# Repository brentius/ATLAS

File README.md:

# ATLAS
*Written in the prophetic perfect tense to give myself some motivation*

ATLAS (Atomic-scale Tunneling and Local Analysis Syste*) is a low-cost scanning tunneling microscope (STM) build inspired by Dimsmary's OpenSTM project (https://github.com/Dimsmary/OpenSTM), with the end goal to accurately image carbon atoms on the lattice of a sample of HOPG.

## File Structure

```
pcb/
code/
cad/
sim/
README.md
LICENSE-HARDWARE
LICENSE-SOFTWARE
.gitignore
```
## Licenses

Hardware design files in `pcb/` and `cad/`, including schematics, PCB layouts,
footprints, and mechanical designs, are licensed under the
[CERN Open Hardware Licence Version 2 – Strongly Reciprocal](LICENSE-HARDWARE)
(`CERN-OHL-S-2.0`). Hardware circuit netlists in `sim/` are covered by the same
license.

Software in `code/` and simulation scripts in `sim/` are licensed under the
[GNU General Public License Version 3](LICENSE-SOFTWARE) (`GPL-3.0-only`).

## How does ATLAS work?
ATLAS is a **scanning tunneling microscope** (STM). Essentially, you have a tip of some hard conductive material (Pt-Ir in this case) that is brought within nanometers of a sample, and very slowly moved along it. As the tip moves along the sample, electrons can tunnel from the atoms in the sample to the tip, which creates a miniscule current. What an STM does is take that current and through PCB wizardry amplify it into something readable, and from that construct a 3D image of the sample at the atomic scale.
# The project itself...
## A bit about this project
*For a more detailed log, refer to my blog at brentius.github.io/blog.*

I first started thinking of this project after my GCSEs in late June 2026, but I really didn't start work until September/October of that year. I'd been (very slowly) working my way through Griffths's *Introduction to Quantum Mechanics* the year before, and I thought it'd be a great idea to simply have fun and play around with quantum tunneling for a bit. I also wanted to do an actual *practical* project, because I absolutely adore PCB design - it's almost theraputic (triggers the same bits of my brain as those iPad games where you need to connect the dots without the lines crossing each other). But before I started any work, the project had to satisfy a few criteria:

1. Is it cool or not? Self explanatory, and I think I made the right choice.
2. Will it kill me? No matter how cool a project, there's not much use in doing it if I die in the process; I'd quite like to stay alive, thank you very much.
3. What can I learn from it? I've always been itching to try my hand at FPGAs, and this project was the perfect opportunity to do so.
4. How expensive will it be? At the end of the day, I don't have infinite funding; if I fry a PCB, or I break a Pt-Ir tip, it's coming out of my own pocket. Not ideal.

The only project that really satisfied all 4 criteria was building an STM, so I got to work on it. I was on vacation in Spain and Sweden during July, so there really wasn't much I could do except for starting to work on the PCBs. And my god, were these a pain.

ATLAS consists of 3 PCBs:
1. **TIA/preamp**. This uses an OPA828 DAC, along with a 100M resistor, to take in the *absolutely miniscule* current from electrons tunneling from the sample to the tip and amplify it by ~10e8 V/A, to get 15 volts running out of the back. This was actually one of the easier PCBs to design, mostly because of how few components there were. The main difficulty in designing the TIA board was physical routing - the current input trace had to be as short as possible and use as little copper as possible, and it also needed to be fenced off with the Great Wall of Vias (there's probably a Latin joke to be made in there but frankly I'm too dumb to make it) to protect it from interference from other traces. This meant that the shape of the board itself was hard to design, as the resistor meant that the board was quite large in both X and Y; considering this had to sit on the scanner block, it was not ideal.
2. **Converter/Pmod carrier**. This was about the point where I figured out I was probably extremely out of my depth. The Converter acts as a translator between the FPGA and the analog circuitry; onboard there's a SAR ADC, which takes the output from the TIA and digitises it for a PID loop. There are also two DAC8734s, that generate the X/Y/Z scan and feedback drive voltages (10 volts). Meanwhile, the AD7521 IC handles the DAC for the stick-slip sliding mechanism. Pmod headers carry SPI and control lines to and from the FPGA. As you can probably tell, this board was an absolute nightmare to design, and is the cause of many sleepless nights I will not get back.
3. **PSU**. All good things need power, and ATLAS is no exception. It runs on 15V - my original design called for a 45V rail to drive the tip movement for maximum range, but I decided against it for redundancy's sake - this project is already complicated enough without splitting 3 power rails (10, 15 and 45V).
### Damping
The PCBs were only one part of the challenge. A STM is an extremely sensitive instrument - after all, it's imaging individual atoms - even someone shouting next to it *will* throw the measurement off. To that end, ATLAS was built in one of the less used classrooms of Winchester College Mill, to keep foot traffic to a minimum; and a large sign was taped to the door telling people to keep their voices down. BUT THAT WASN'T ENOUGH! Any vibrations of the table would also throw the tip off by millimeters (matters a lot on the nanometer scale), so the whole system had to be on a damper.

The initial damper concept uses a frame, 8 springs and a 12lb slab of granite supporting the scanner assembly. The slab weight is adjustable rather than a fixed design requirement. No spring-rate or frequency measurement is recorded here, so the earlier 1Hz estimate is unverified. The [suspension calculation](sim/atlas_mechanics/SUSPENSION_BUDGET.md) and [comparison with other STM isolation designs](sim/atlas_mechanics/ISOLATION_OPTIONS.md) set out a modular trial of the spring stage, optional magnetic eddy-current damping and a short plate stack. Wind, sound and cable disturbances still need physical testing. I briefly considered building an enclosure with ANC, but I ultimately decided against it - the last thing I need is another signal processing challenge. It would be fun though...
## Assembly
*The instructions provided below are but a summary, and your version of ATLAS will probably not work if you just follow these. For a more detailed set of instructions, or if you'd like to see how I did it, please refer to brentius.github.io/blog.*

A full bill of materials can be found at ```BOM.md```.
### Part I. The Scanner Block
This is the scanner block - i.e. the block that actually does the scanning. One of the main insights I lifted from OpenSTM was to use a buzzer and a stick-slip mechanism to slowly increment the position of the tip, which franly I think was an insight of genius. Why a buzzer? While your typical linear actuators and belt drives work for 3D printing or CNC milling, an STM requires nanometer precision, which you physically can't achieve with a linear actuator. There's also the problem that linear actuators produce heat, which at nanometer scales, really throws the position off due to the joints expanding/contracting. We first quarter the 
#### Preparing the tip
Version 1 of ATLAS used a length of 80:20 Pt-Ir (platinum-iridium) wire that I simply cut at 45 degrees with a pair of sharp cutters. Boring, but it works.
# Meta Stuff
## Acknowledgements
# References

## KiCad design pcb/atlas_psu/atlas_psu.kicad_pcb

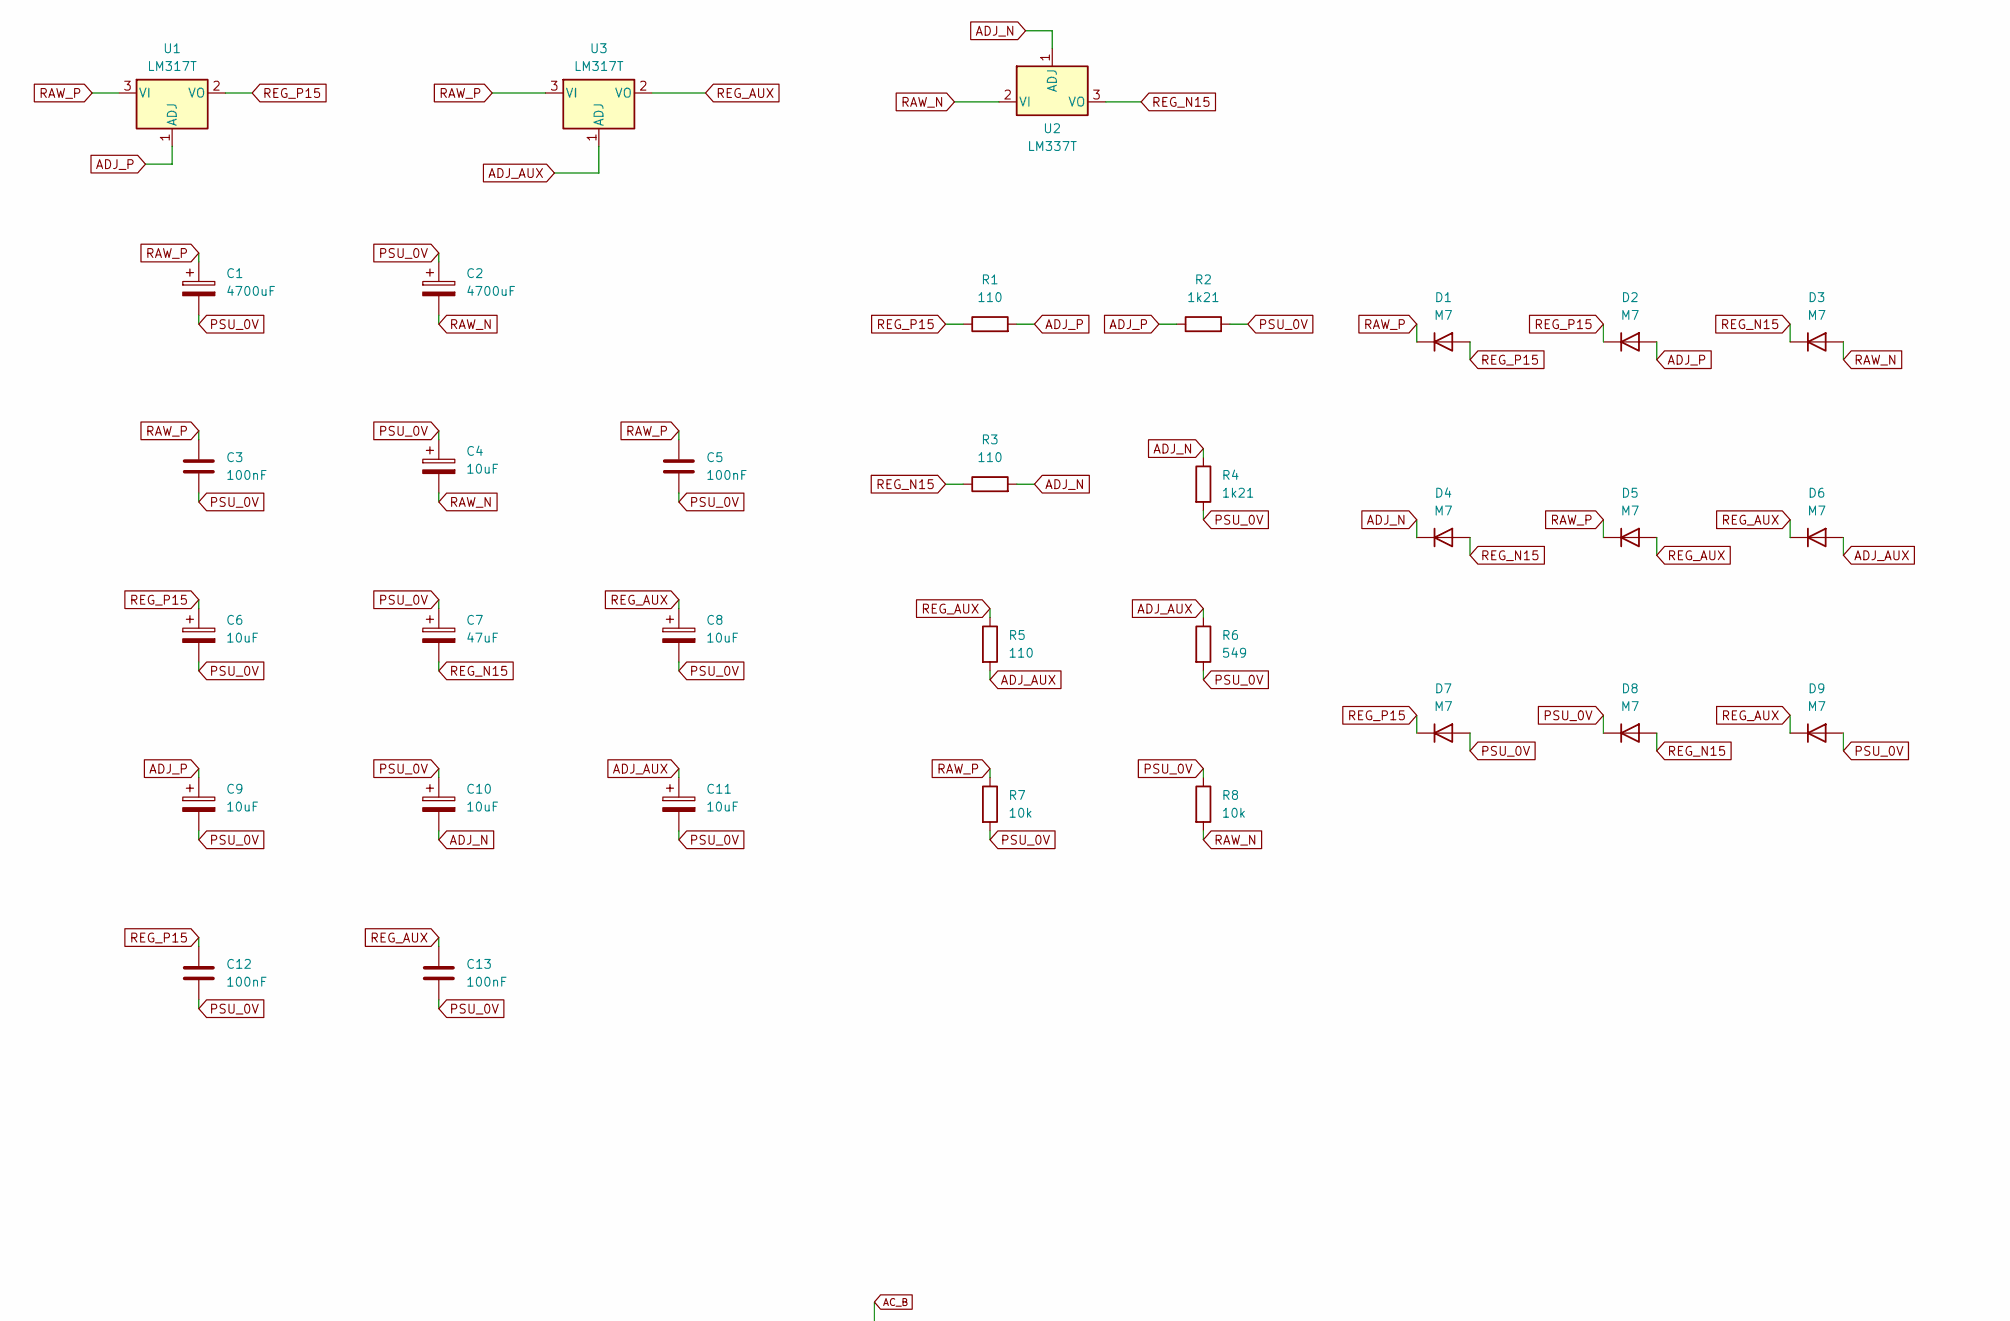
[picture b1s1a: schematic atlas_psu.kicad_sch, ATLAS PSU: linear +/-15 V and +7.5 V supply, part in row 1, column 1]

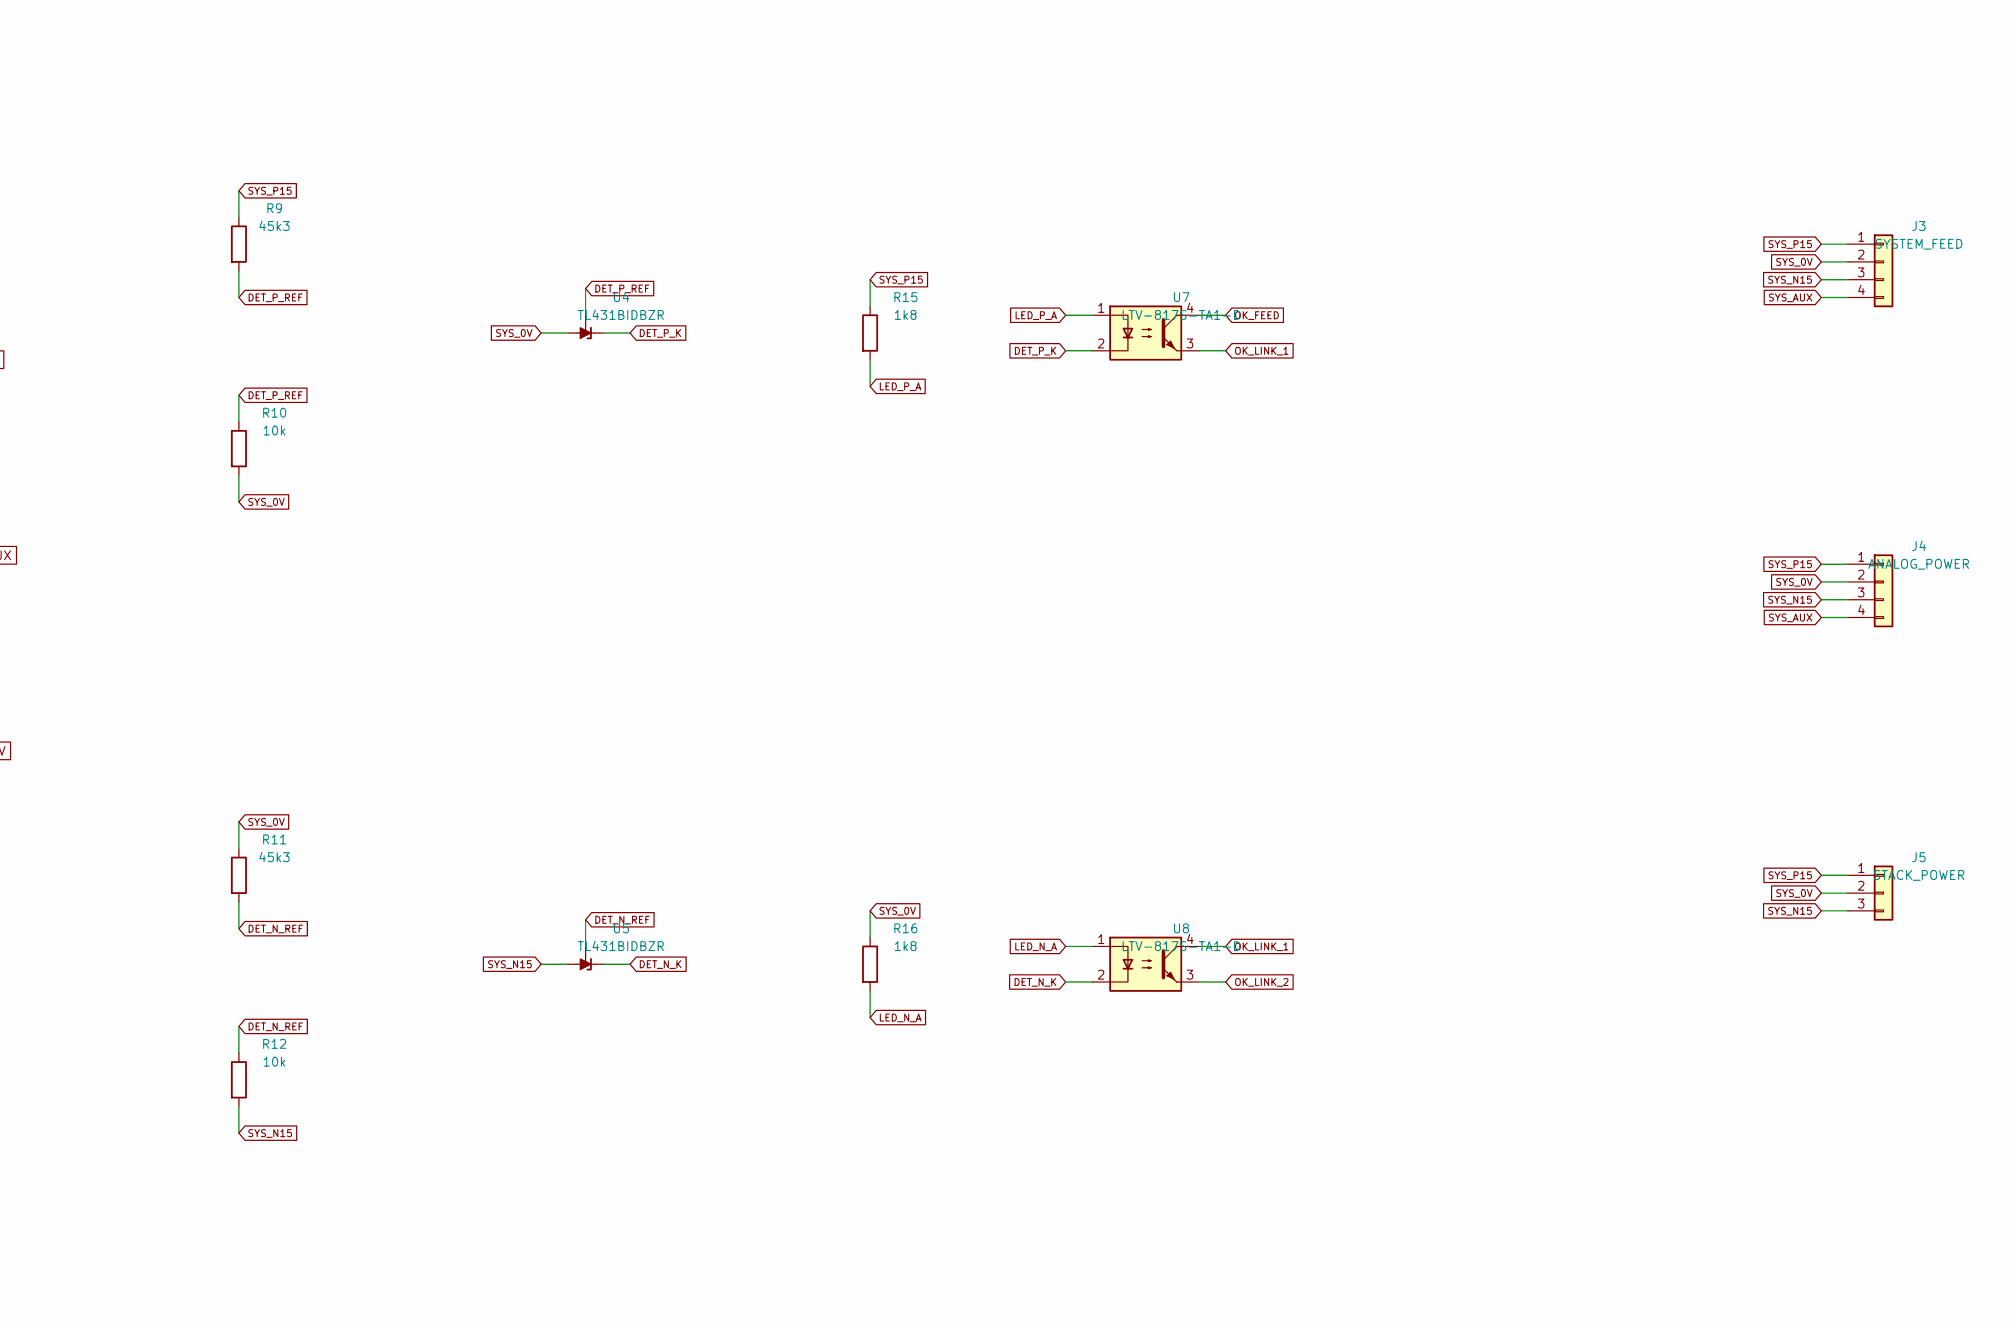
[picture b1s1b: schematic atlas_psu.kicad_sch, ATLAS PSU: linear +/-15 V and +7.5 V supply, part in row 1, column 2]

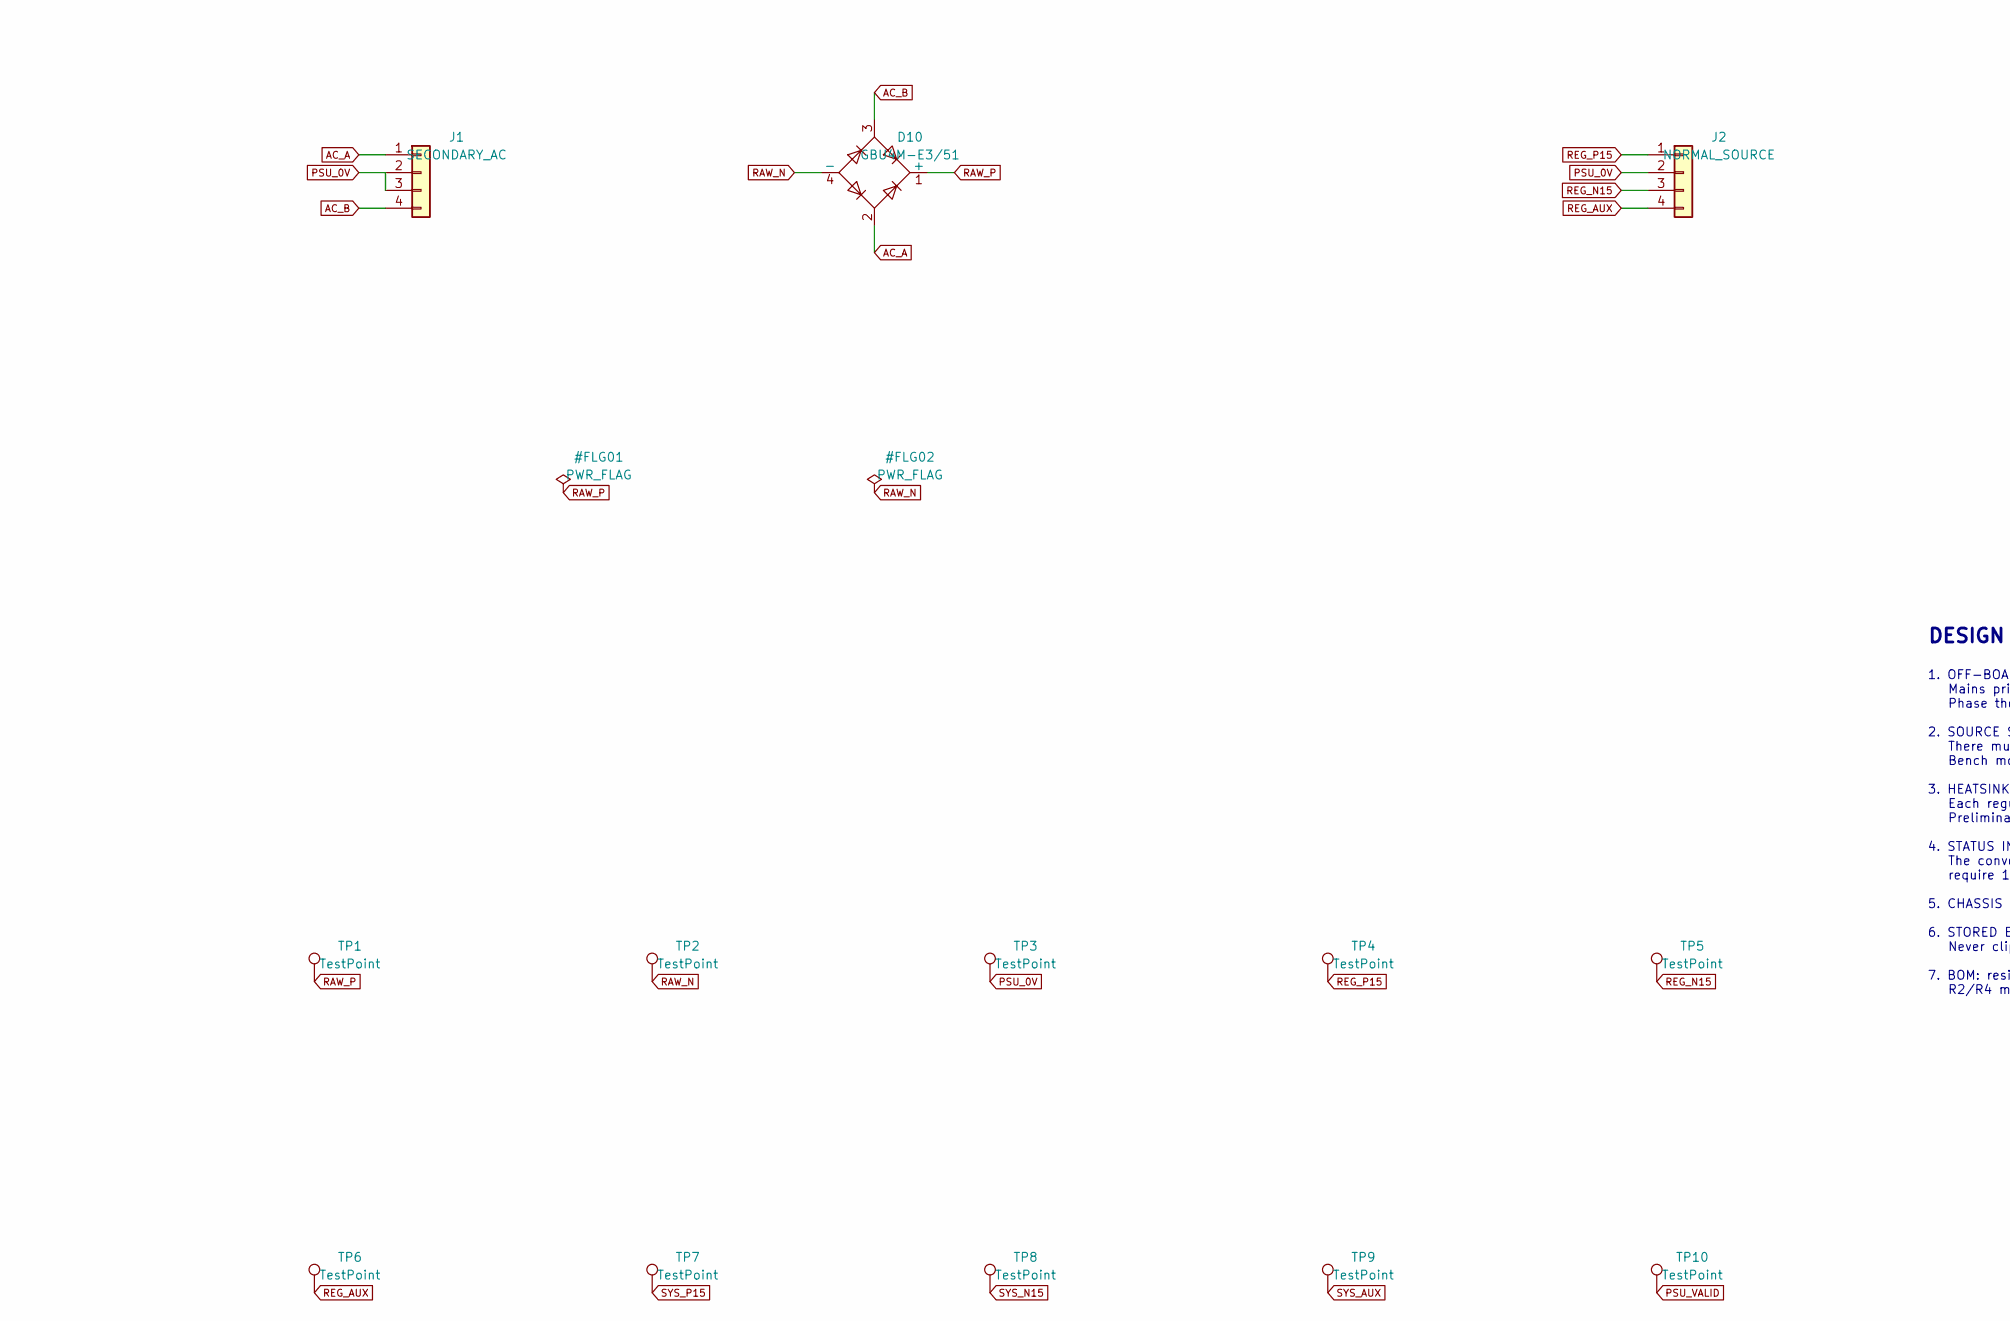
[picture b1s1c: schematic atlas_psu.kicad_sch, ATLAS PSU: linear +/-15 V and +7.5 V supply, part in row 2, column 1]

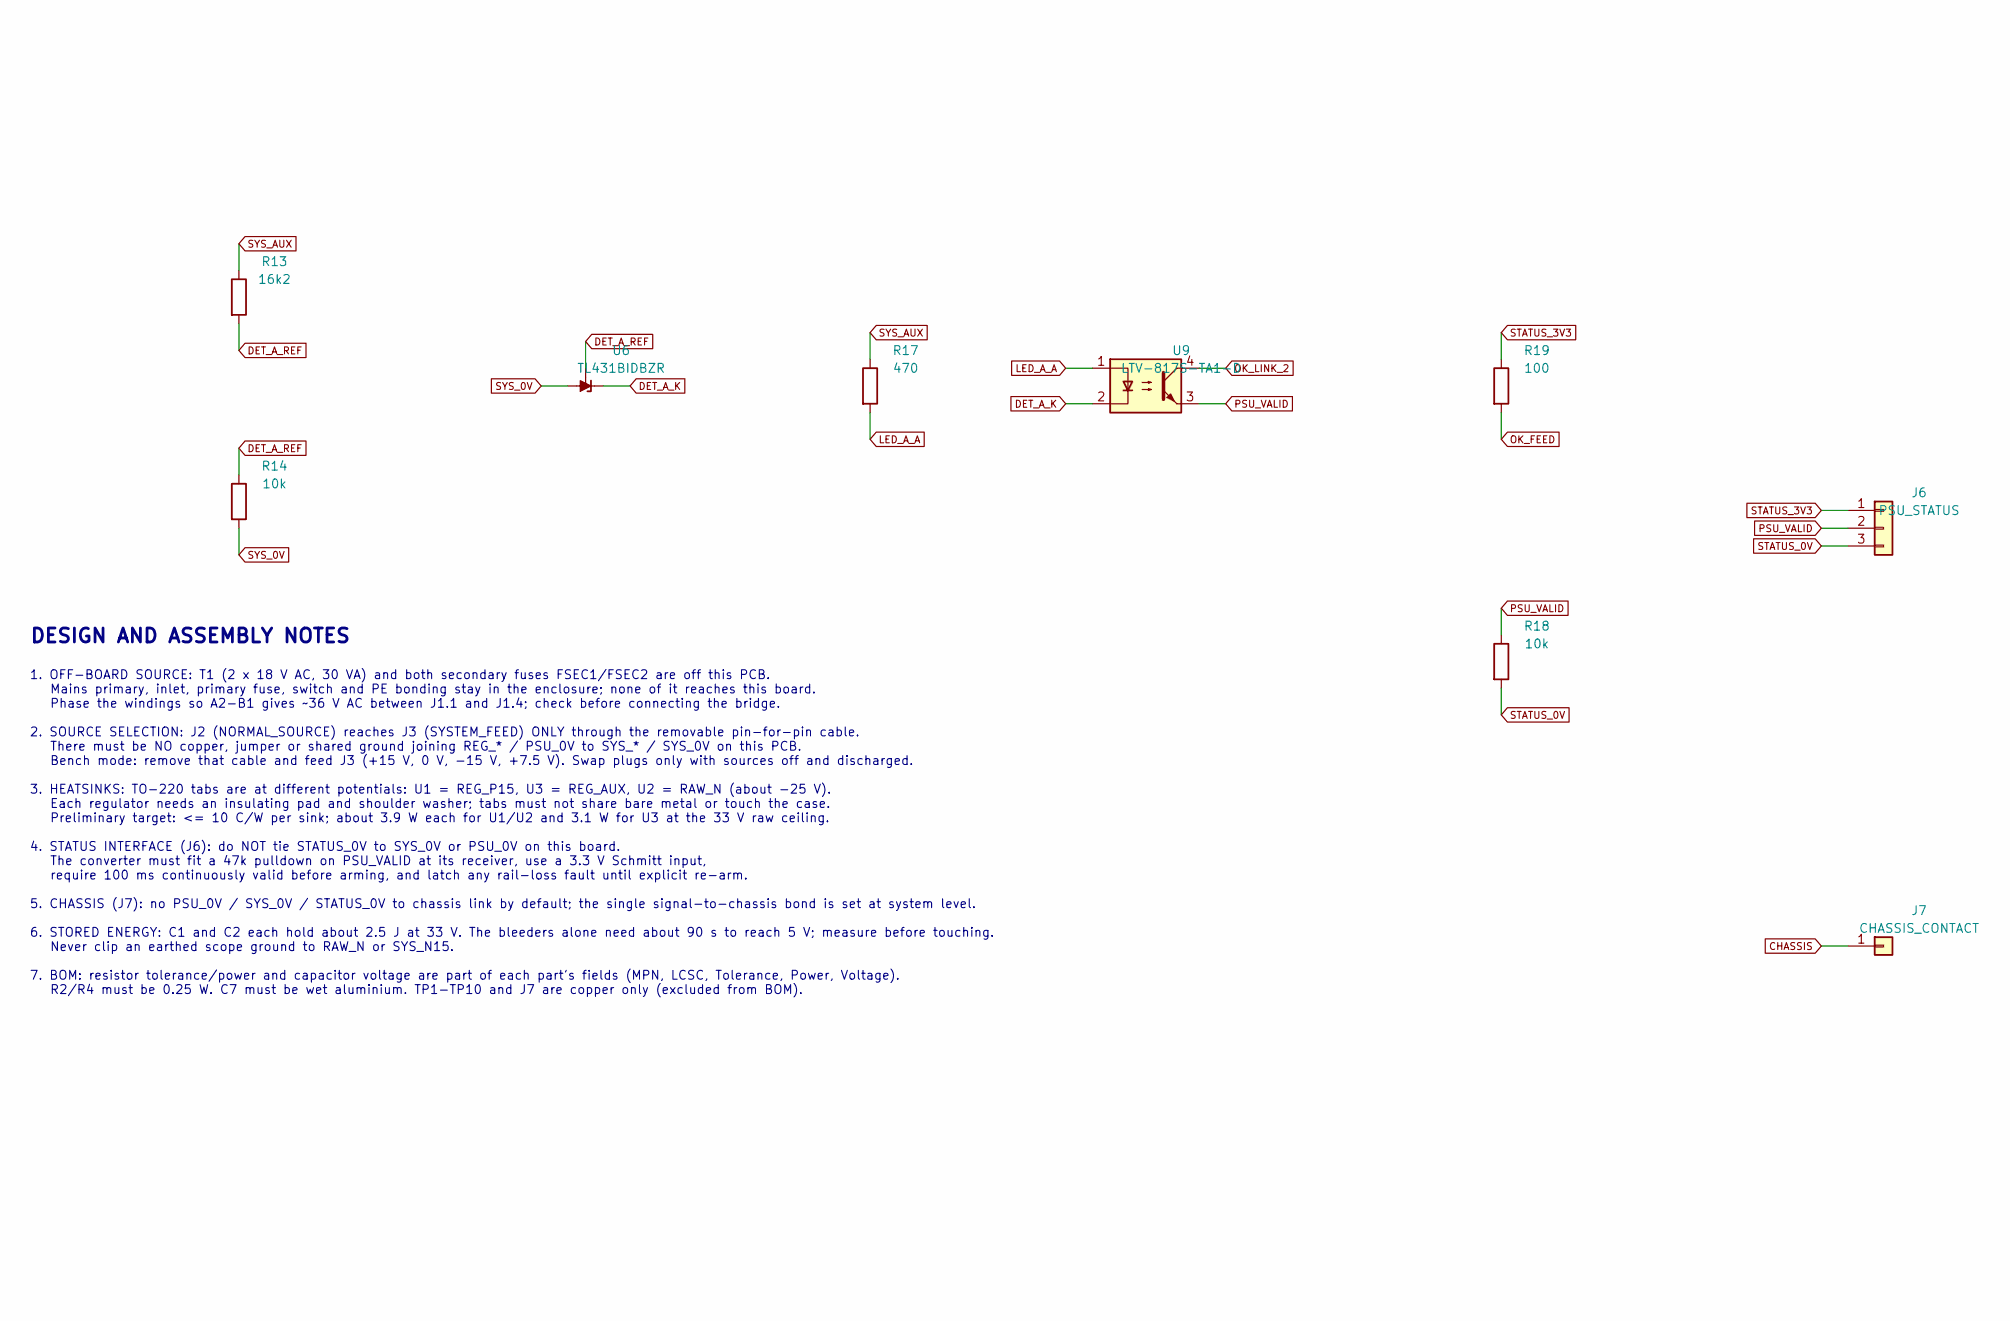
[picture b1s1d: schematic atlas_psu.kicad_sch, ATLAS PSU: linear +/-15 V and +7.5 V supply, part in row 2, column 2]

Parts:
C1, C2: 4700uF; CP_Radial_D30.0mm_P10.00mm_SnapIn; Tolerance 20%; Voltage 50V; MPN LGY1H472MELB30; LCSC C1582310
C3, C5, C12, C13: 100nF; C_0603_1608Metric; Tolerance 10%; Voltage 50V; MPN CL10B104KB8NNNC; LCSC C1591
C4, C6, C8, C9, C10, C11: 10uF; CP_Elec_6.3x5.4_Nichicon; Tolerance 20%; Voltage 50V; MPN UWT1H100MCL1GB; LCSC C445064
C7: 47uF; CP_Elec_6.3x7.7; Tolerance 20%; Voltage 50V; MPN UWT1H470MCL1GS; LCSC C445060
D1, D2, D3, D4, D5, D6, D7, D8, D9: M7; D_SMA; MPN M7; LCSC C95872
D10: GBU4M-E3/51; Diode_Bridge_Vishay_GBU; MPN GBU4M-E3/51; LCSC C3008977
J1: SECONDARY_AC; TerminalBlock_Phoenix_MKDS-1,5-4-5.08_1x04_P5.08mm_Horizont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; MPN MKDS 1,5/4-5,08
J2: NORMAL_SOURCE; JST_XH_B4B-XH-A_1x04_P2.50mm_Vertical; MPN B4B-XH-A; LCSC C41422491
J3: SYSTEM_FEED; JST_XH_B4B-XH-A_1x04_P2.50mm_Vertical; MPN B4B-XH-A; LCSC C41422491
J4: ANALOG_POWER; JST_XH_B4B-XH-A_1x04_P2.50mm_Vertical; MPN B4B-XH-A; LCSC C41422491
J5: STACK_POWER; JST_XH_B3B-XH-A_1x03_P2.50mm_Vertical; MPN B3B-XH-A(LF)(SN); LCSC C144394
J6: PSU_STATUS; JST_GH_SM03B-GHS-TB_1x03-1MP_P1.25mm_Horizontal; MPN SM03B-GHS-TB(LF)(SN); LCSC C514175
J7: CHASSIS_CONTACT; SolderWirePad_1x01_SMD_1.5x3mm
R1, R3, R5: 110; R_0603_1608Metric; Tolerance 0.1%; MPN RN73R1JTTD1100B25; LCSC C2508454
R2, R4: 1k21; R_0805_2012Metric; Tolerance 0.1%; MPN ERA-6VEB1211V; LCSC C3986344
R6: 549; R_0805_2012Metric; Tolerance 0.1%; MPN ERA-6AEB5490V; LCSC C2087831
R7, R8: 10k; R_2010_5025Metric; Tolerance 5%; MPN 2010W2J0103T4S; LCSC C20349
R9, R11: 45k3; R_0603_1608Metric; Tolerance 0.1%; MPN ERA-3AEB4532V; LCSC C3951453
R10, R12, R14, R18: 10k; R_0603_1608Metric; Tolerance 1%; MPN 0603WAF1002T5E; LCSC C25804
R13: 16k2; R_0603_1608Metric; Tolerance 1%; MPN RTT031622FTP; LCSC C103329
R15, R16: 1k8; R_1206_3216Metric; Tolerance 1%; MPN CRCW12061K80FKEBC; LCSC C4211031
R17: 470; R_1206_3216Metric; Tolerance 1%; MPN CR1206F44700G; LCSC C102199
R19: 100; R_0603_1608Metric; Tolerance 1%; MPN 0603WAF1000T5E; LCSC C22775
TP1, TP2, TP3, TP4, TP5, TP6, TP7, TP8, TP9, TP10: TestPoint; TestPoint_Pad_D1.0mm
U1, U3: LM317T; TO-220-3_Vertical; MPN LM317T; LCSC C39583120
U2: LM337T; TO-220-3_Vertical; MPN LM337T; LCSC C5345
U4, U5, U6: TL431BIDBZR; SOT-23; MPN TL431BIDBZR; LCSC C41283
U7, U8, U9: LTV-817S-TA1-D; SMDIP-4_W9.53mm; MPN LTV-817S-TA1-D; LCSC C114603

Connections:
AC_A: D10.2, J1.1
AC_B: D10.3, J1.4
ADJ_AUX: C11.1, D6.2 (A), R5.2, R6.1, U3.1 (ADJ)
ADJ_N: C10.2, D4.1 (K), R3.2, R4.1, U2.1 (ADJ)
ADJ_P: C9.1, D2.2 (A), R1.2, R2.1, U1.1 (ADJ)
CHASSIS: J7.1 (Pin_1_1)
DET_A_K: U6.1 (K), U9.2
DET_A_REF: R13.2, R14.1, U6.2 (REF)
DET_N_K: U5.1 (K), U8.2
DET_N_REF: R11.2, R12.1, U5.2 (REF)
DET_P_K: U4.1 (K), U7.2
DET_P_REF: R9.2, R10.1, U4.2 (REF)
LED_A_A: R17.2, U9.1
LED_N_A: R16.2, U8.1
LED_P_A: R15.2, U7.1
OK_FEED: R19.2, U7.4
OK_LINK_1: U7.3, U8.4
OK_LINK_2: U8.3, U9.4
PSU_0V: C1.2, C2.1, C3.2, C4.1, C5.2, C6.2, C7.1, C8.2, C9.2, C10.1, C11.2, C12.2, C13.2, D7.2 (A), D8.1 (K), D9.2 (A), J1.2, J1.3, J2.2, R2.2, R4.2, R6.2, R7.2, R8.1, TP3.1 (1_1)
PSU_VALID: J6.2, R18.1, TP10.1 (1_1), U9.3
RAW_N: C2.2, C4.2, D3.2 (A), D10.4 (-), R8.2, TP2.1 (1_1), U2.2 (VI)
RAW_P: C1.1, C3.1, C5.1, D1.1 (K), D5.1 (K), D10.1 (+), R7.1, TP1.1 (1_1), U1.3 (VI), U3.3 (VI)
REG_AUX: C8.1, C13.1, D5.2 (A), D6.1 (K), D9.1 (K), J2.4, R5.1, TP6.1 (1_1), U3.2 (VO)
REG_N15: C7.2, D3.1 (K), D4.2 (A), D8.2 (A), J2.3, R3.1, TP5.1 (1_1), U2.3 (VO)
REG_P15: C6.1, C12.1, D1.2 (A), D2.1 (K), D7.1 (K), J2.1, R1.1, TP4.1 (1_1), U1.2 (VO)
STATUS_0V: J6.3, R18.2
STATUS_3V3: J6.1, R19.1
SYS_0V: J3.2, J4.2, J5.2, R10.2, R11.1, R14.2, R16.1, U4.3 (A), U6.3 (A)
SYS_AUX: J3.4, J4.4, R13.1, R17.1, TP9.1 (1_1)
SYS_N15: J3.3, J4.3, J5.3, R12.2, TP8.1 (1_1), U5.3 (A)
SYS_P15: J3.1, J4.1, J5.1, R9.1, R15.1, TP7.1 (1_1)

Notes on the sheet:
DESIGN AND ASSEMBLY NOTES
1. OFF-BOARD SOURCE: T1 (2 x 18 V AC, 30 VA) and both secondary fuses FSEC1/FSEC2 are off this PCB. Mains primary, inlet, primary fuse, switch and PE bonding stay in the enclosure; none of it reaches this board. Phase the windings so A2-B1 gives ~36 V AC between J1.1 and J1.4; check before connecti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

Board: 2 copper layers, 68 parts (0 on the bottom side), 30 nets, no tracks yet.

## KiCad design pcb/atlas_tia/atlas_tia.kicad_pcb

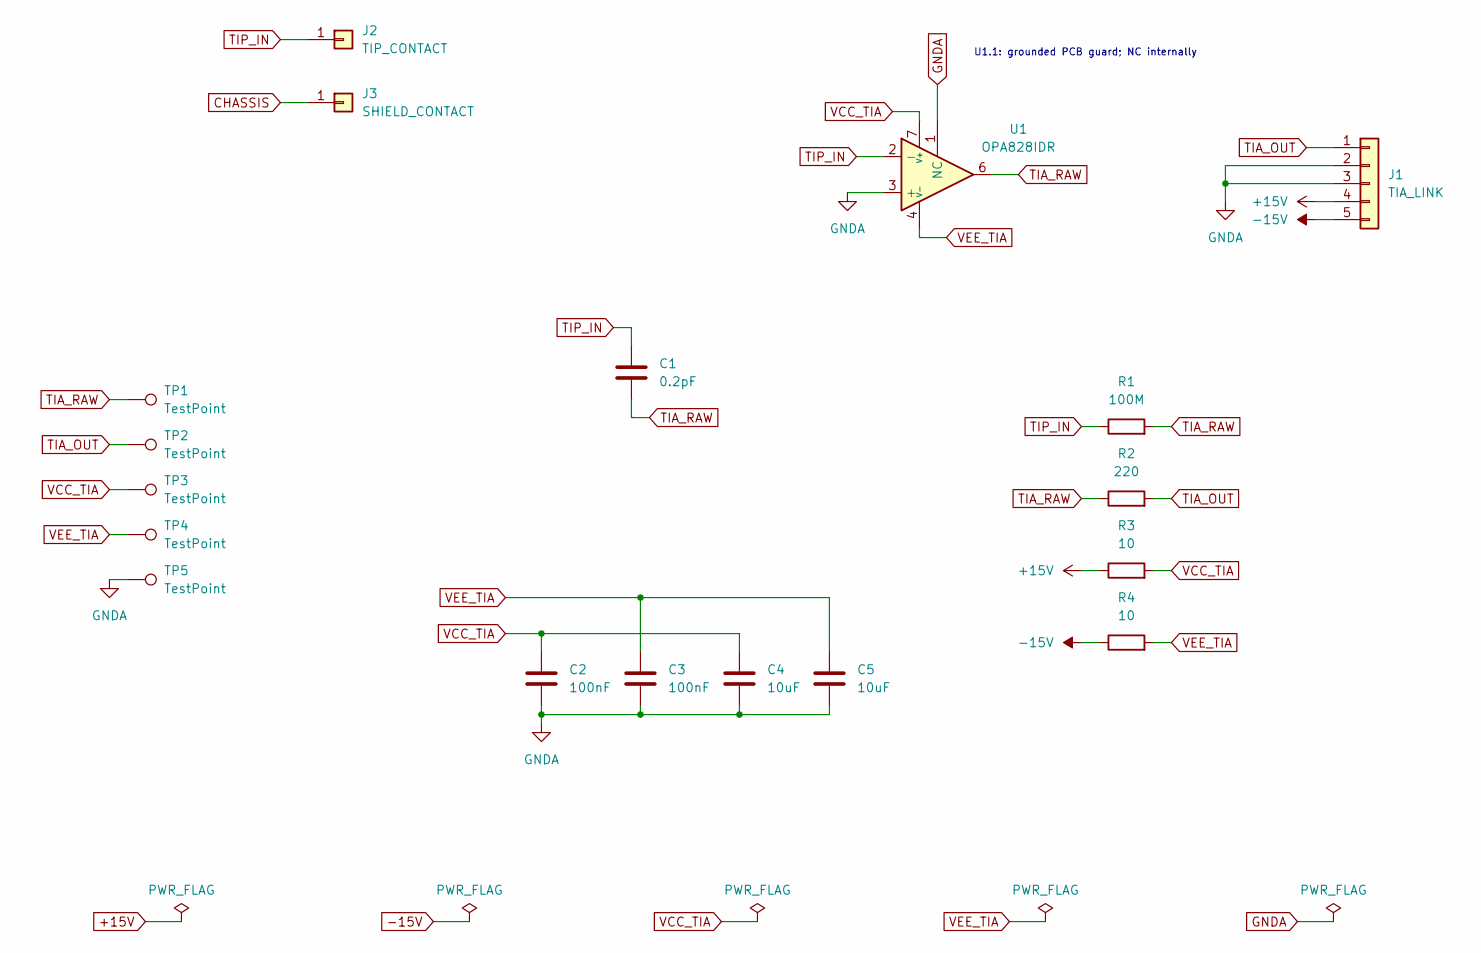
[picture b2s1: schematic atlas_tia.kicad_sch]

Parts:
C1: 0.2pF; C_0603_1608Metric_Guard; Voltage 50V; Tolerance ±0.1pF; MPN CQ0603BRNPO9BNR20
C2, C3: 100nF; C_0603_1608Metric; Voltage 50V
C4, C5: 10uF; C_1210_3225Metric; Voltage 50V
J1: TIA_LINK; JST_GH_SM05B-GHS-TB_1x05-1MP_P1.25mm_Horizontal; MPN SM05B-GHS-TB
J2: TIP_CONTACT; SolderWirePad_1x01_SMD_1x2mm
J3: SHIELD_CONTACT; SolderWirePad_1x01_SMD_1.5x3mm
R1: 100M; R_1206_3216Metric_Guard; Tolerance 1%
R2: 220; R_0603_1608Metric; Tolerance 1%
R3, R4: 10; R_0603_1608Metric; Tolerance 1%
TP1, TP2, TP3, TP4, TP5: TestPoint; TestPoint_Pad_D1.0mm
U1: OPA828IDR; SOIC-8_3.9x4.9mm_P1.27mm_Guard

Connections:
+15V: J1.4, R3.1
-15V: J1.5, R4.1
CHASSIS: J3.1 (Pin_1_1)
GNDA: C2.2, C3.2, C4.2, C5.2, J1.2, J1.3, TP5.1 (1_1), U1.1 (NC), U1.3 (+)
TIA_OUT: J1.1, R2.2, TP2.1 (1_1)
TIA_RAW: C1.2, R1.2, R2.1, TP1.1 (1_1), U1.6
TIP_IN: C1.1, J2.1 (Pin_1_1), R1.1, U1.2 (-)
VCC_TIA: C2.1, C4.1, R3.2, TP3.1 (1_1), U1.7 (V+)
VEE_TIA: C3.1, C5.1, R4.2, TP4.1 (1_1), U1.4 (V-)

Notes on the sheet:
U1.1: grounded PCB guard; NC internally

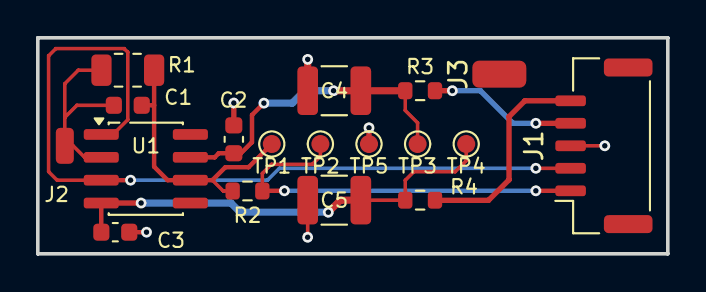
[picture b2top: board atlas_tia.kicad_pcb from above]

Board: 2 copper layers, 35.0 x 12.0 mm, 18 parts (0 on the bottom side), 8 nets.
